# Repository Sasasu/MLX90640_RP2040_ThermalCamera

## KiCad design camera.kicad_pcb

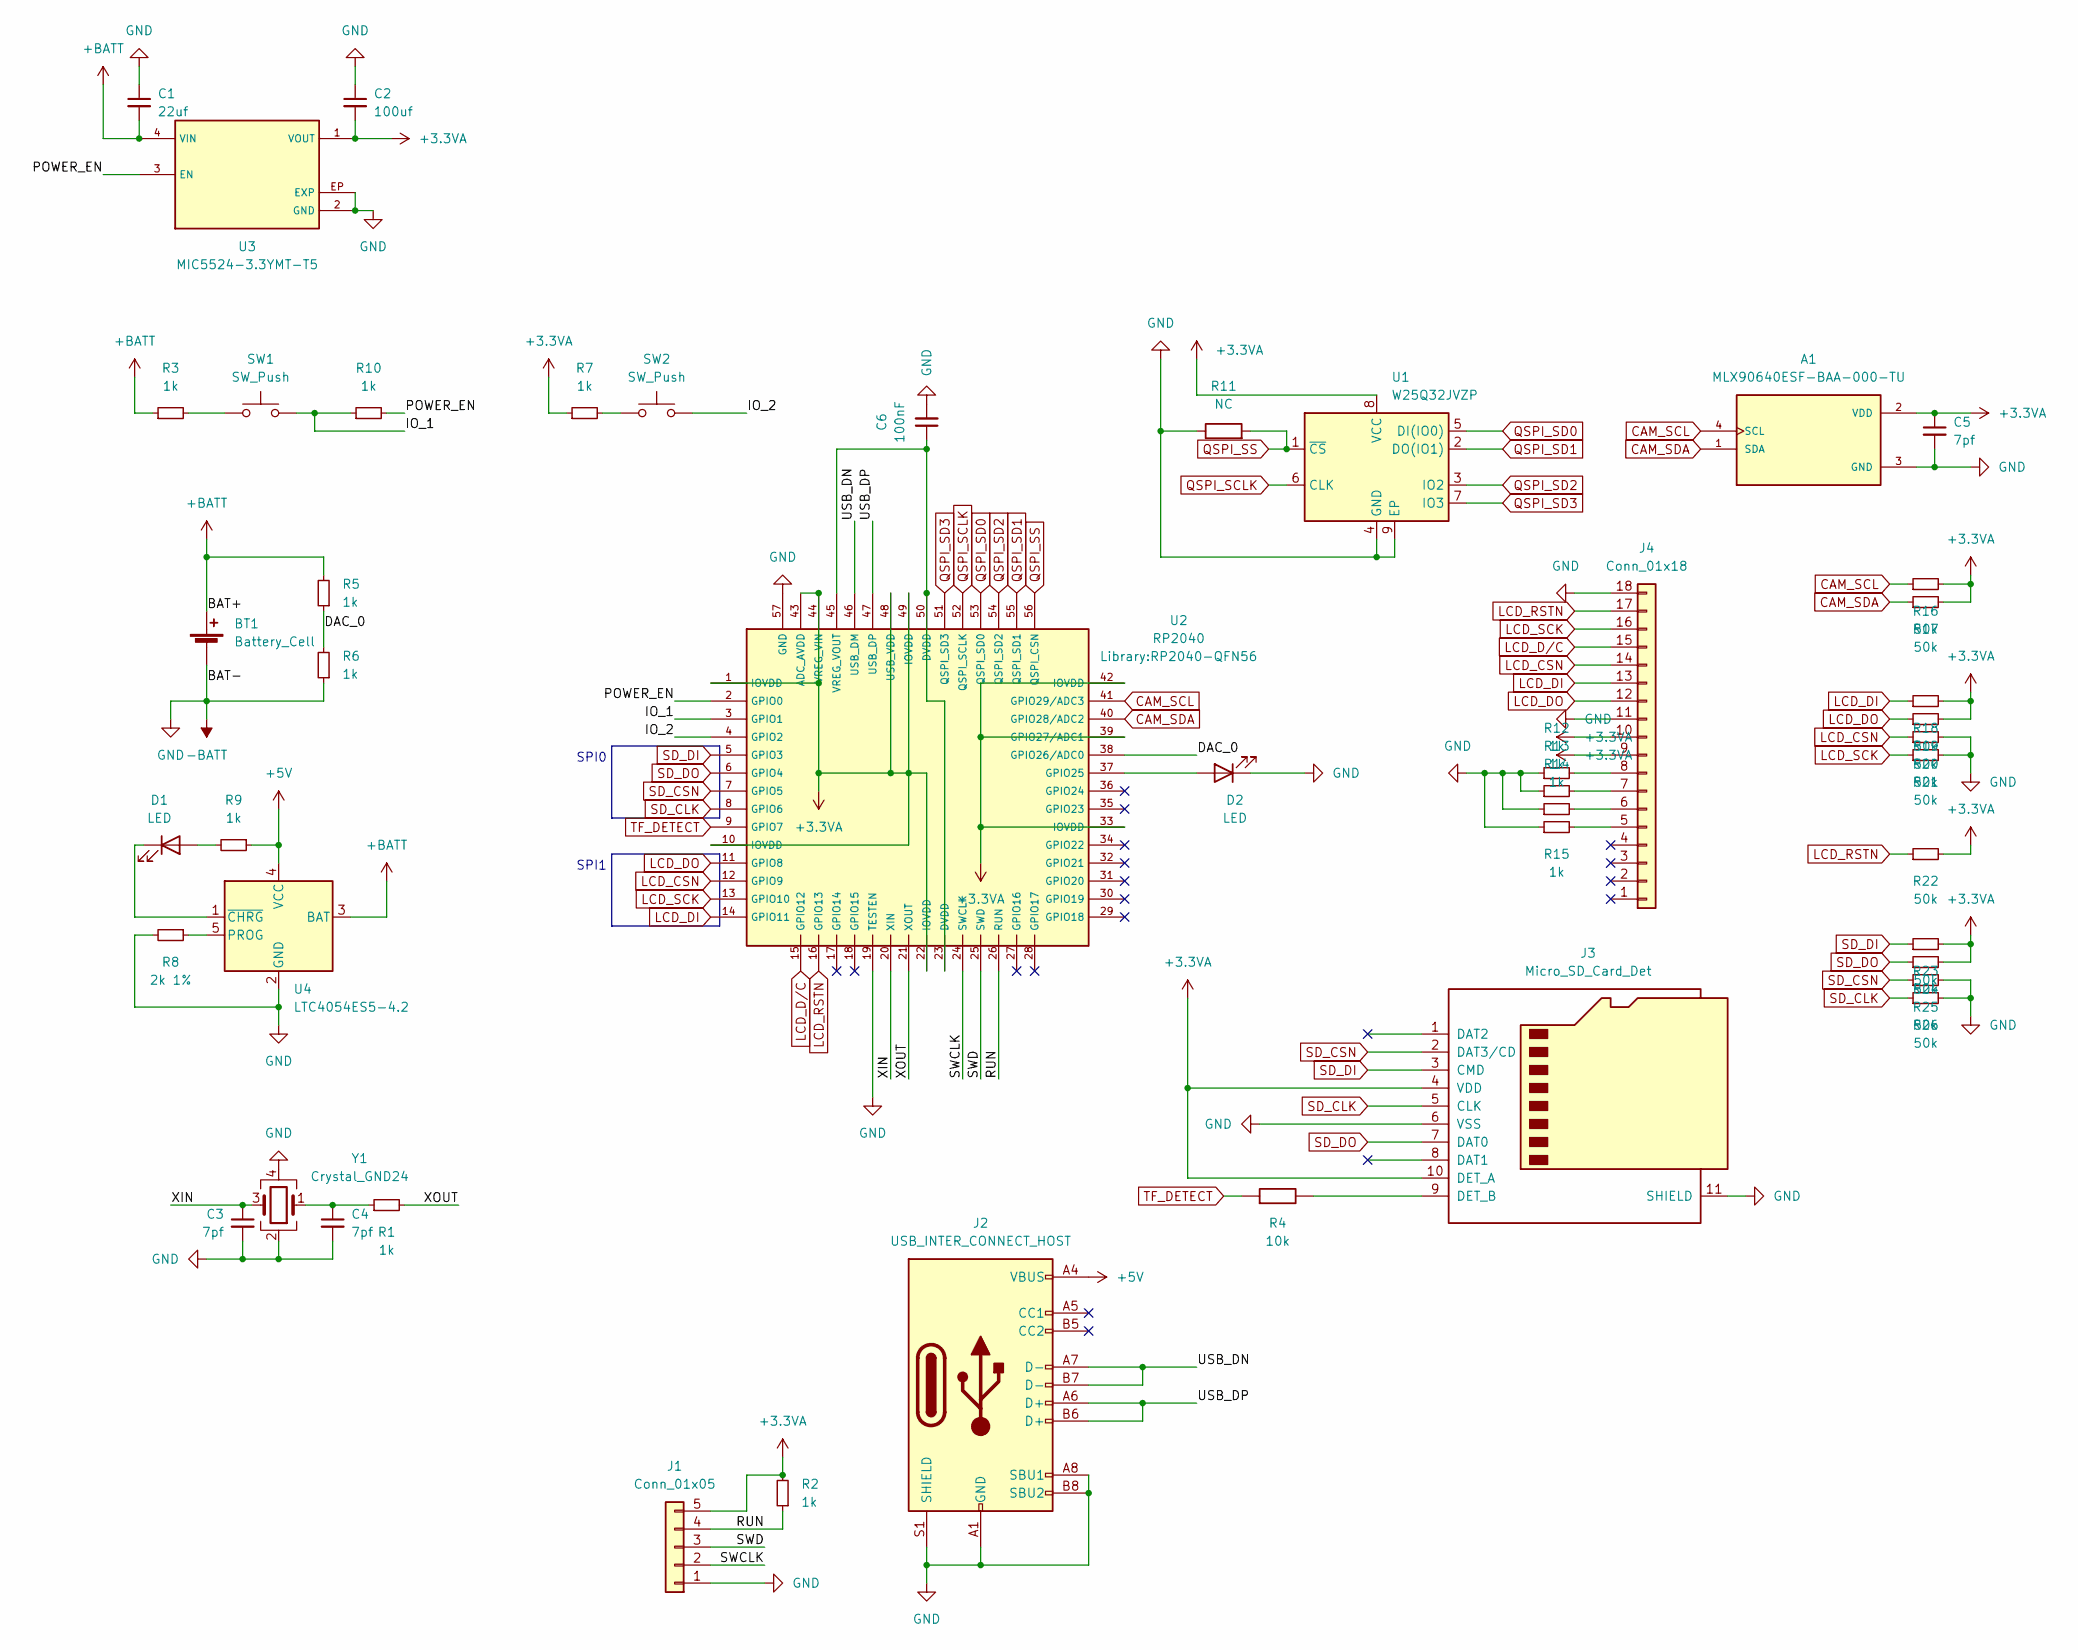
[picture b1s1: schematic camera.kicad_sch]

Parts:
A1: MLX90640ESF-BAA-000-TU; TO292P930H600-4; PARTREV 11
BT1: Battery_Cell; PinHeader_1x2_P2.54mm
C1: 22uf; C_0603_1608Metric
C2: 100uf; C_1206_3216Metric
C3, C4, C5: 7pf; C_0402_1005Metric
C6: 100nF; C_0402_1005Metric_Pad0.74x0.62mm_HandSolder
D1, D2: LED; LED_0402_1005Metric
J1: Conn_01x05; PinHeader_1x05_P2.54mm_Vertical
J2: USB_INTER_CONNECT_HOST; USB_C_Receptacle_Palconn_UTC16-G
J3: Micro_SD_Card_Det; microSD_HC_Molex_104031-0811
J4: Conn_01x18; FPC 01x18 0.4mm
R1, R2, R3, R5, R6, R7, R9, R10, R12, R13, R14, R15: 1k; R_0402_1005Metric
R4: 10k; R_0402_1005Metric
R8: 2k 1%; R_0402_1005Metric
R11: NC; R_0402_1005Metric
R16, R17, R18, R19, R20, R21, R22, R23, R24, R25, R26: 50k; R_0402_1005Metric
SW1, SW2: SW_Push; YD-3410
U1: W25Q32JVZP; WSON-8-1EP_6x5mm_P1.27mm_EP3.4x4.3mm
U2: RP2040; RP2040-QFN56
U3: MIC5524-3.3YMT-T5
U4: LTC4054ES5-4.2; TSOT-23-5
Y1: Crystal_GND24; Crystal_SMD_3225-4Pin_3.2x2.5mm

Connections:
+3.3VA: A1.2 (VDD), C2.2, C5.1, J1.5, J3.4 (VDD), J3.10 (DET_A), J4.9, J4.10, R2.2, R7.1, R16.2, R17.2, R18.2, R19.2, R22.2, R23.2, R24.2, U1.8 (VCC), U2.1 (IOVDD), U2.10 (IOVDD), U2.22 (IOVDD), U2.33 (IOVDD), U2.39 (GPIO27/ADC1), U2.42 (IOVDD), U2.43 (ADC_AVDD), U2.44 (VREG_VIN), U2.48 (USB_VDD), U2.49 (IOVDD), U3.1 (VOUT)
+5V: J2.A4 (VBUS), J2.A9 (VBUS), J2.B4 (VBUS), J2.B9 (VBUS), R9.1, U4.4 (VCC)
+BATT: BT1.1 (+), C1.2, R3.1, R5.2, U3.4 (VIN), U4.3 (BAT)
-BATT: A1.3 (GND), BT1.2 (-), C1.1, C2.1, C3.2, C4.2, C5.2, C6.2, D2.1 (K), J1.1, J2.A1 (GND), J2.A8 (SBU1), J2.A12 (GND), J2.B1 (GND), J2.B8 (SBU2), J2.B12 (GND), J2.S1 (SHIELD), J3.6 (VSS), J3.11 (SHIELD), J4.11, J4.18, R6.1, R8.2, R11.1, R12.1, R13.1, R14.1, R15.1, R20.2, R21.2, R25.2, R26.2, U1.4 (GND), U1.9 (EP), U2.19 (TESTEN), U2.57 (GND), U3.2 (GND), U3.EP (EXP), U4.2 (GND), Y1.2, Y1.4
/DAC_0: R5.1, R6.2, U2.38 (GPIO26/ADC0)
/IO_1: R10.1, SW1.2, U2.3 (GPIO1)
/IO_2: SW2.2, U2.4 (GPIO2)
/POWER_EN: R10.2, U2.2 (GPIO0), U3.3 (EN)
/RUN: J1.4, R2.1, U2.26 (RUN)
/SWCLK: J1.2, U2.24 (SWCLK)
/SWD: J1.3, U2.25 (SWD)
/USB_DN: J2.A7 (D-), J2.B7 (D-), U2.46 (USB_DM)
/USB_DP: J2.A6 (D+), J2.B6 (D+), U2.47 (USB_DP)
/XIN: C3.1, U2.20 (XIN), Y1.3
/XOUT: R1.2, U2.21 (XOUT)
CAM_SCL: A1.4 (SCL), R16.1, U2.41 (GPIO29/ADC3)
CAM_SDA: A1.1 (SDA), R17.1, U2.40 (GPIO28/ADC2)
LCD_CSN: J4.14, R20.1, U2.12 (GPIO9)
LCD_DI: J4.13, R18.1, U2.14 (GPIO11)
LCD_DO: J4.12, R19.1, U2.11 (GPIO8)
LCD_D/C: J4.15, U2.15 (GPIO12)
LCD_RSTN: J4.17, R22.1, U2.16 (GPIO13)
LCD_SCK: J4.16, R21.1, U2.13 (GPIO10)
unnamed: C4.1, R1.1, Y1.1
unnamed: D1.2 (A), R9.2
unnamed: D1.1 (K), U4.1 (~CHRG)
unnamed: D2.2 (A), U2.37 (GPIO25)
unnamed: J3.9 (DET_B), R4.1
unnamed: J4.5, R15.2
unnamed: J4.6, R14.2
unnamed: J4.7, R13.2
unnamed: J4.8, R12.2
unnamed: R3.2, SW1.1
unnamed: R7.2, SW2.1
unnamed: C6.1, U2.23 (DVDD), U2.45 (VREG_VOUT), U2.50 (DVDD)
unnamed: R8.1, U4.5 (PROG)
QSPI_SCLK: U1.6 (CLK), U2.52 (QSPI_SCLK)
QSPI_SD0: U1.5 (DI(IO0)), U2.53 (QSPI_SD0)
QSPI_SD1: U1.2 (DO(IO1)), U2.55 (QSPI_SD1)
QSPI_SD2: U1.3 (IO2), U2.54 (QSPI_SD2)
QSPI_SD3: U1.7 (IO3), U2.51 (QSPI_SD3)
QSPI_SS: R11.2, U1.1 (~CS), U2.56 (QSPI_CSN)
SD_CLK: J3.5 (CLK), R26.1, U2.8 (GPIO6)
SD_CSN: J3.2 (DAT3/CD), R25.1, U2.7 (GPIO5)
SD_DI: J3.3 (CMD), R23.1, U2.5 (GPIO3)
SD_DO: J3.7 (DAT0), R24.1, U2.6 (GPIO4)
TF_DETECT: R4.2, U2.9 (GPIO7)

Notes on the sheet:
SPI0
SPI1

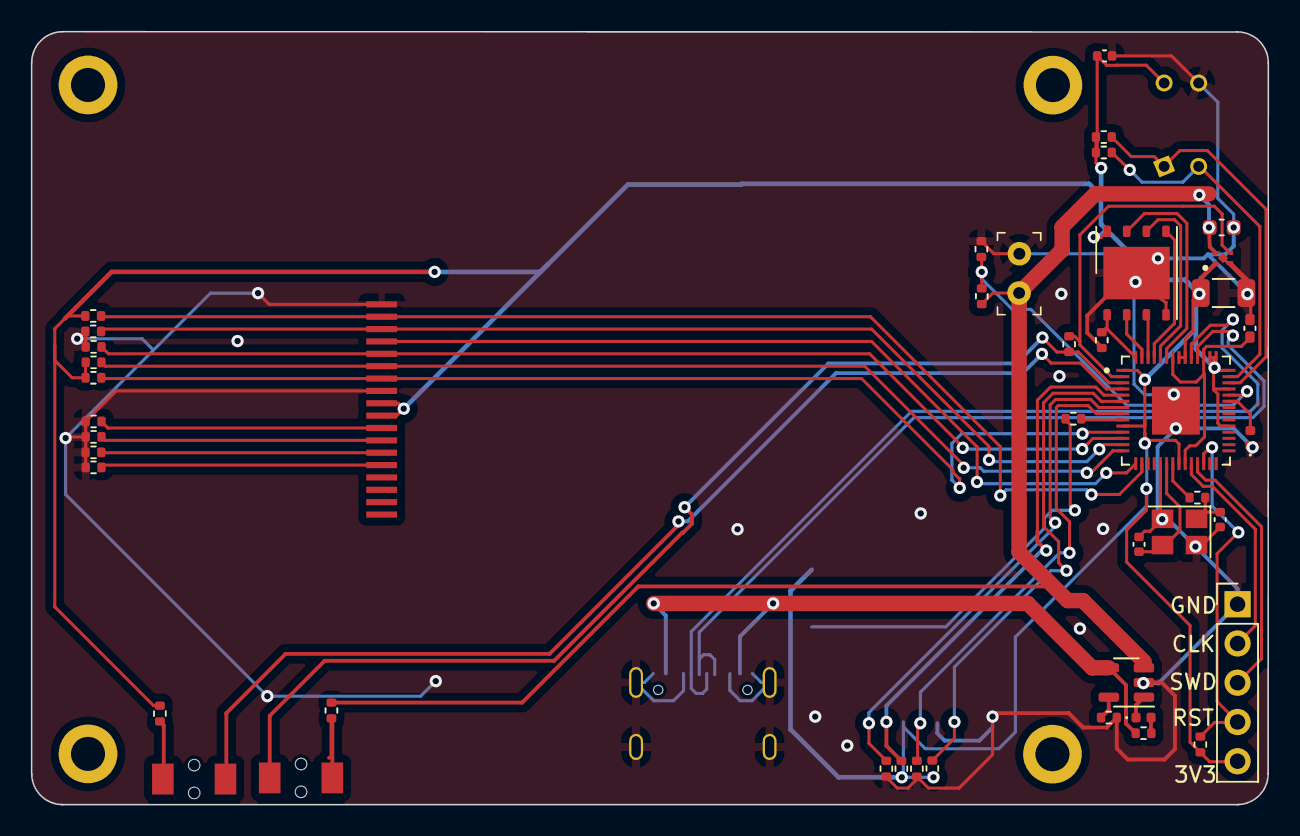
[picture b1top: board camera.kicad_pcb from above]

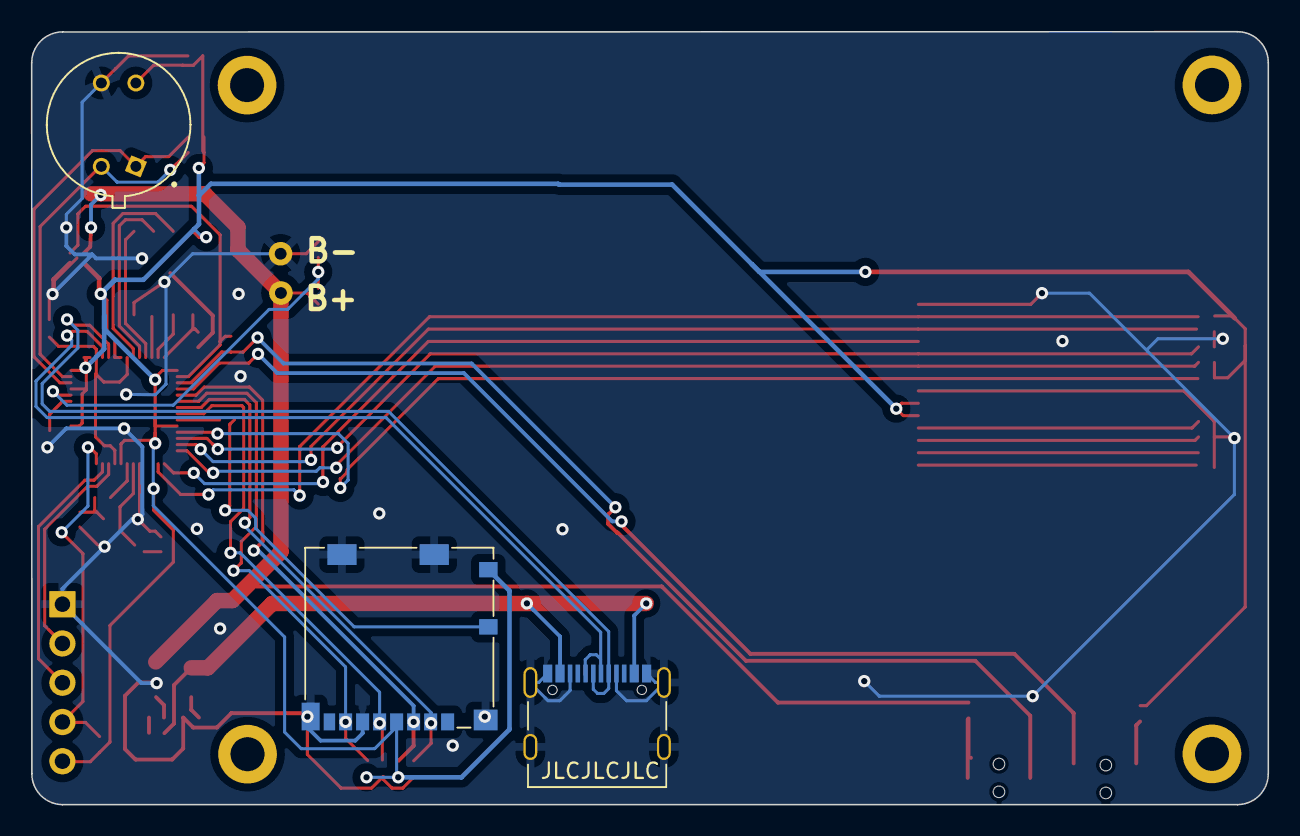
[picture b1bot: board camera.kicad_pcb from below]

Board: 2 copper layers, 80.0 x 50.0 mm, 47 parts (3 on the bottom side), 47 nets.

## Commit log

2023-04-11 add readme
